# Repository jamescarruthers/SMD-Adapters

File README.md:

# SMD Adapters

As yet unteseted; https://oshpark.com/projects/TcK31JN6

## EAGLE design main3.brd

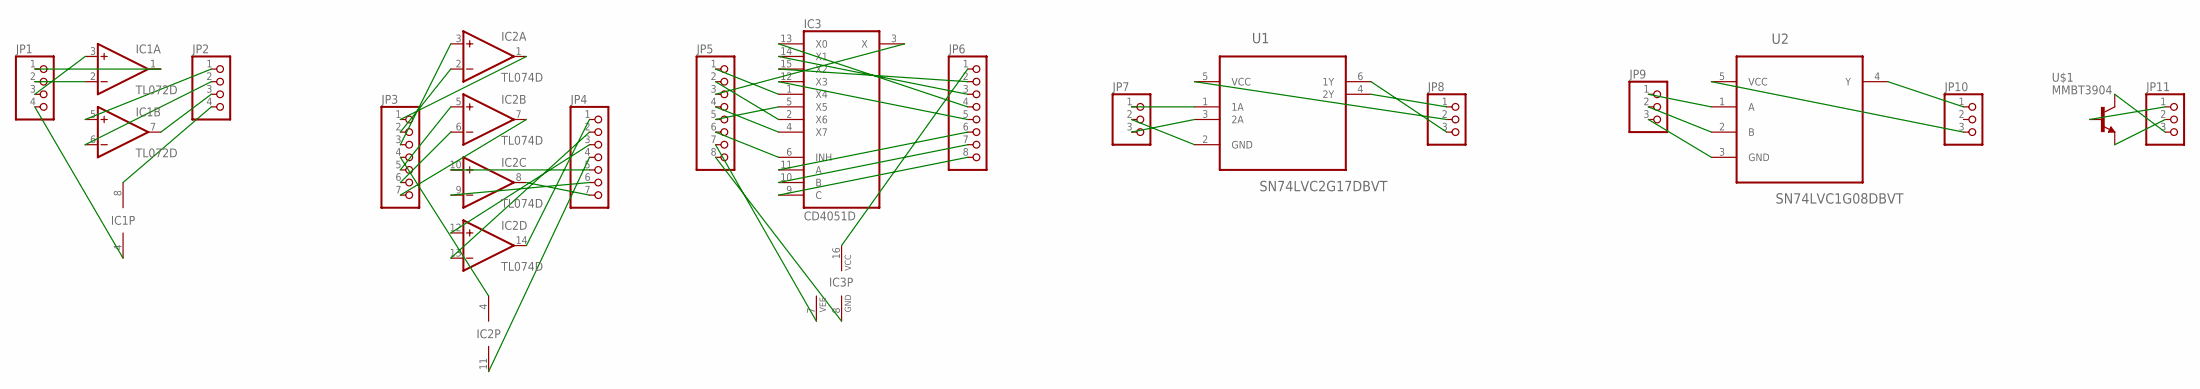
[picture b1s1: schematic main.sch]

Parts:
IC1: TL072D; SO08
IC2: TL074D; SO14
IC3: CD4051D; SO16
JP1, JP2: PINHD-1X4/OCT; 1X04/OCT
JP3, JP4: PINHD-1X7/OCT; 1X07/OCT
JP5, JP6: PINHD-1X8; 1X08
JP7, JP8, JP9, JP10, JP11: PINHD-1X3/OCT; 1X03/OCT
U1: SN74LVC2G17DBVT; SOT95P280X145-6N
U2: SN74LVC1G08DBVT; SOT95P280X145-5N
U$1: MMBT3904; SOT23

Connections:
unnamed: IC1.1 (OUT), JP1.1
unnamed: IC1.2 (-IN), JP1.2
unnamed: IC1.3 (+IN), JP1.3
unnamed: IC1.4 (V-), JP1.4
unnamed: IC1.5 (+IN), JP2.1
unnamed: IC1.6 (-IN), JP2.2
unnamed: IC1.7 (OUT), JP2.3
unnamed: IC1.8 (V+), JP2.4
unnamed: IC2.1 (OUT), JP3.1
unnamed: IC2.2 (-IN), JP3.2
unnamed: IC2.3 (+IN), JP3.3
unnamed: IC2.4 (V+), JP3.4
unnamed: IC2.5 (+IN), JP3.5
unnamed: IC2.6 (-IN), JP3.6
unnamed: IC2.7 (OUT), JP3.7
unnamed: IC2.8 (OUT), JP4.7
unnamed: IC2.9 (-IN), JP4.6
unnamed: IC2.10 (+IN), JP4.5
unnamed: IC2.11 (V-), JP4.4
unnamed: IC2.12 (+IN), JP4.3
unnamed: IC2.13 (-IN), JP4.2
unnamed: IC2.14 (OUT), JP4.1
unnamed: IC3.1 (X4), JP5.1
unnamed: IC3.2 (X6), JP5.2
unnamed: IC3.3 (X), JP5.3
unnamed: IC3.4 (X7), JP5.4
unnamed: IC3.5 (X5), JP5.5
unnamed: IC3.6 (INH), JP5.6
unnamed: IC3.7 (VEE), JP5.7
unnamed: IC3.8 (GND), JP5.8
unnamed: IC3.9 (C), JP6.8
unnamed: IC3.10 (B), JP6.7
unnamed: IC3.11 (A), JP6.6
unnamed: IC3.12 (X3), JP6.5
unnamed: IC3.13 (X0), JP6.4
unnamed: IC3.14 (X1), JP6.3
unnamed: IC3.15 (X2), JP6.2
unnamed: IC3.16 (VCC), JP6.1
unnamed: JP7.1, U1.1 (1A)
unnamed: JP7.2, U1.2 (GND)
unnamed: JP7.3, U1.3 (2A)
unnamed: JP8.1, U1.4 (2Y)
unnamed: JP8.2, U1.5 (VCC)
unnamed: JP8.3, U1.6 (1Y)
unnamed: JP9.1, U2.1 (A)
unnamed: JP9.2, U2.2 (B)
unnamed: JP9.3, U2.3 (GND)
unnamed: JP10.1, U2.4 (Y)
unnamed: JP10.3, U2.5 (VCC)
unnamed: JP11.1, U$1.1 (B)
unnamed: JP11.2, U$1.2 (E)
unnamed: JP11.3, U$1.3 (C)

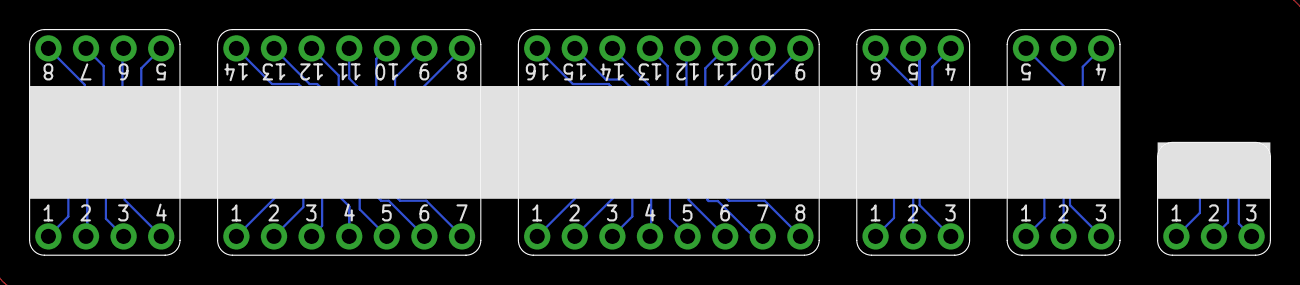
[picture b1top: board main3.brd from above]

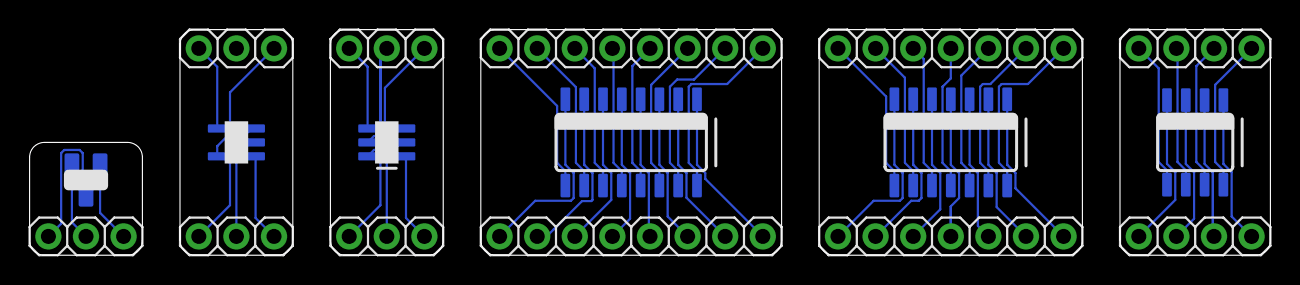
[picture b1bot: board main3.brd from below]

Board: 2 copper layers, 83.8 x 15.2 mm, 17 parts (17 on the bottom side), 52 nets.

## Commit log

2017-04-25 Rename main3.brd to main.brd
2017-04-25 Rename main3.sch to main.sch
